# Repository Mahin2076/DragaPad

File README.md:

# DragaPad
This is the hackpad i made! Something that is speacial about it is that it has multiple colors and it has a dragon design on the top part of the case!!!!. It also has 6 button functions. I hope you like it :3

## Features
- Six key design
- RGB LED status lighting
- Customizable keycaps
- Compact and portable

## Overview

## PCB Layout

## Schematic

## Case

# Bill of Materials (BOM)
## Components List

| Reference | Quantity | Description | Package/Type | Notes |
|-----------|----------|-------------|--------------|-------|
| U1 | 1 | XIAO-RP2040-DIP | DIP-14 | Seeed Studio XIAO RP2040 in DIP format |
| SW1-SW6 | 6 | Tactile Push Button Switch | Through-hole | Momentary, normally open |
| D1, D3 | 2 | SK6812MINI RGB LED | 3535 SMD | Addressable RGB LEDs |
| x | 1 | 3d Printed Case | x | Will be printed on my personal printer |

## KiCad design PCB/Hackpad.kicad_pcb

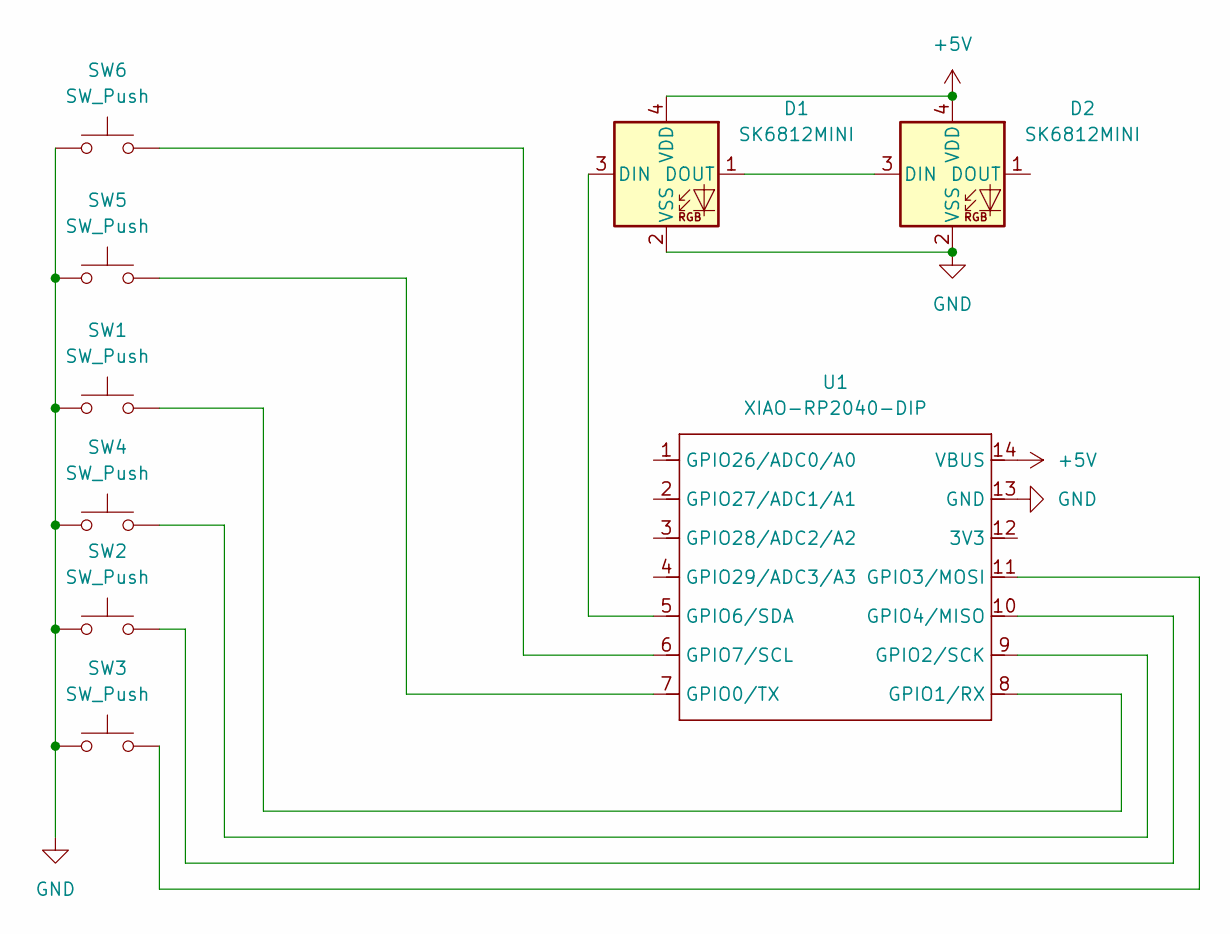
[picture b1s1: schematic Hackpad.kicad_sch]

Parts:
D1, D2: SK6812MINI; LED_SK6812MINI_PLCC4_3.5x3.5mm_P1.75mm
SW1, SW2, SW3, SW4, SW5, SW6: SW_Push; SW_Cherry_MX_1.00u_PCB
U1: XIAO-RP2040-DIP

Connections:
+5V: D1.4 (VDD), D2.4 (VDD), U1.14 (VBUS)
GND: D1.2 (VSS), D2.2 (VSS), SW1.1, SW2.1, SW3.1, SW4.1, SW5.1, SW6.1, U1.13 (GND)
unnamed: D1.3 (DIN), U1.5 (GPIO6/SDA)
unnamed: D1.1 (DOUT), D2.3 (DIN)
unnamed: SW5.2, U1.7 (GPIO0/TX)
unnamed: SW1.2, U1.8 (GPIO1/RX)
unnamed: SW4.2, U1.9 (GPIO2/SCK)
unnamed: SW3.2, U1.11 (GPIO3/MOSI)
unnamed: SW2.2, U1.10 (GPIO4/MISO)
unnamed: SW6.2, U1.6 (GPIO7/SCL)

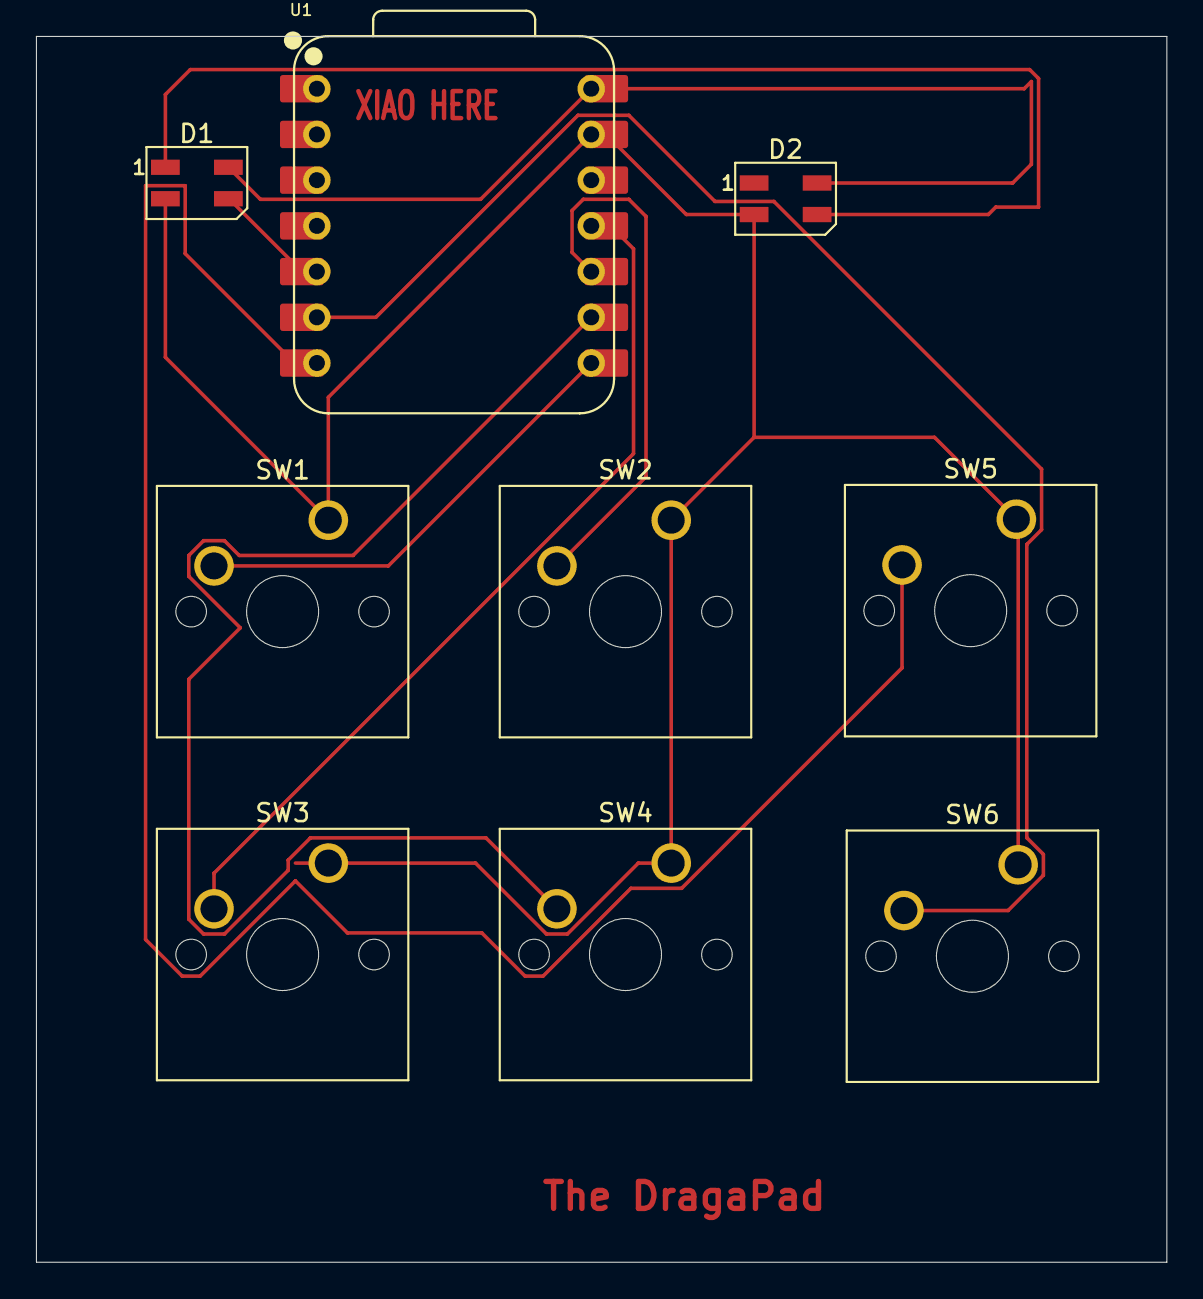
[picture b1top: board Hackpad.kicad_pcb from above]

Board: 2 copper layers, 62.8 x 68.1 mm, 9 parts (0 on the bottom side), 10 nets.

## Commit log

2025-07-10 MAIN.PY
2025-07-10 case.step
2025-07-10 hello
